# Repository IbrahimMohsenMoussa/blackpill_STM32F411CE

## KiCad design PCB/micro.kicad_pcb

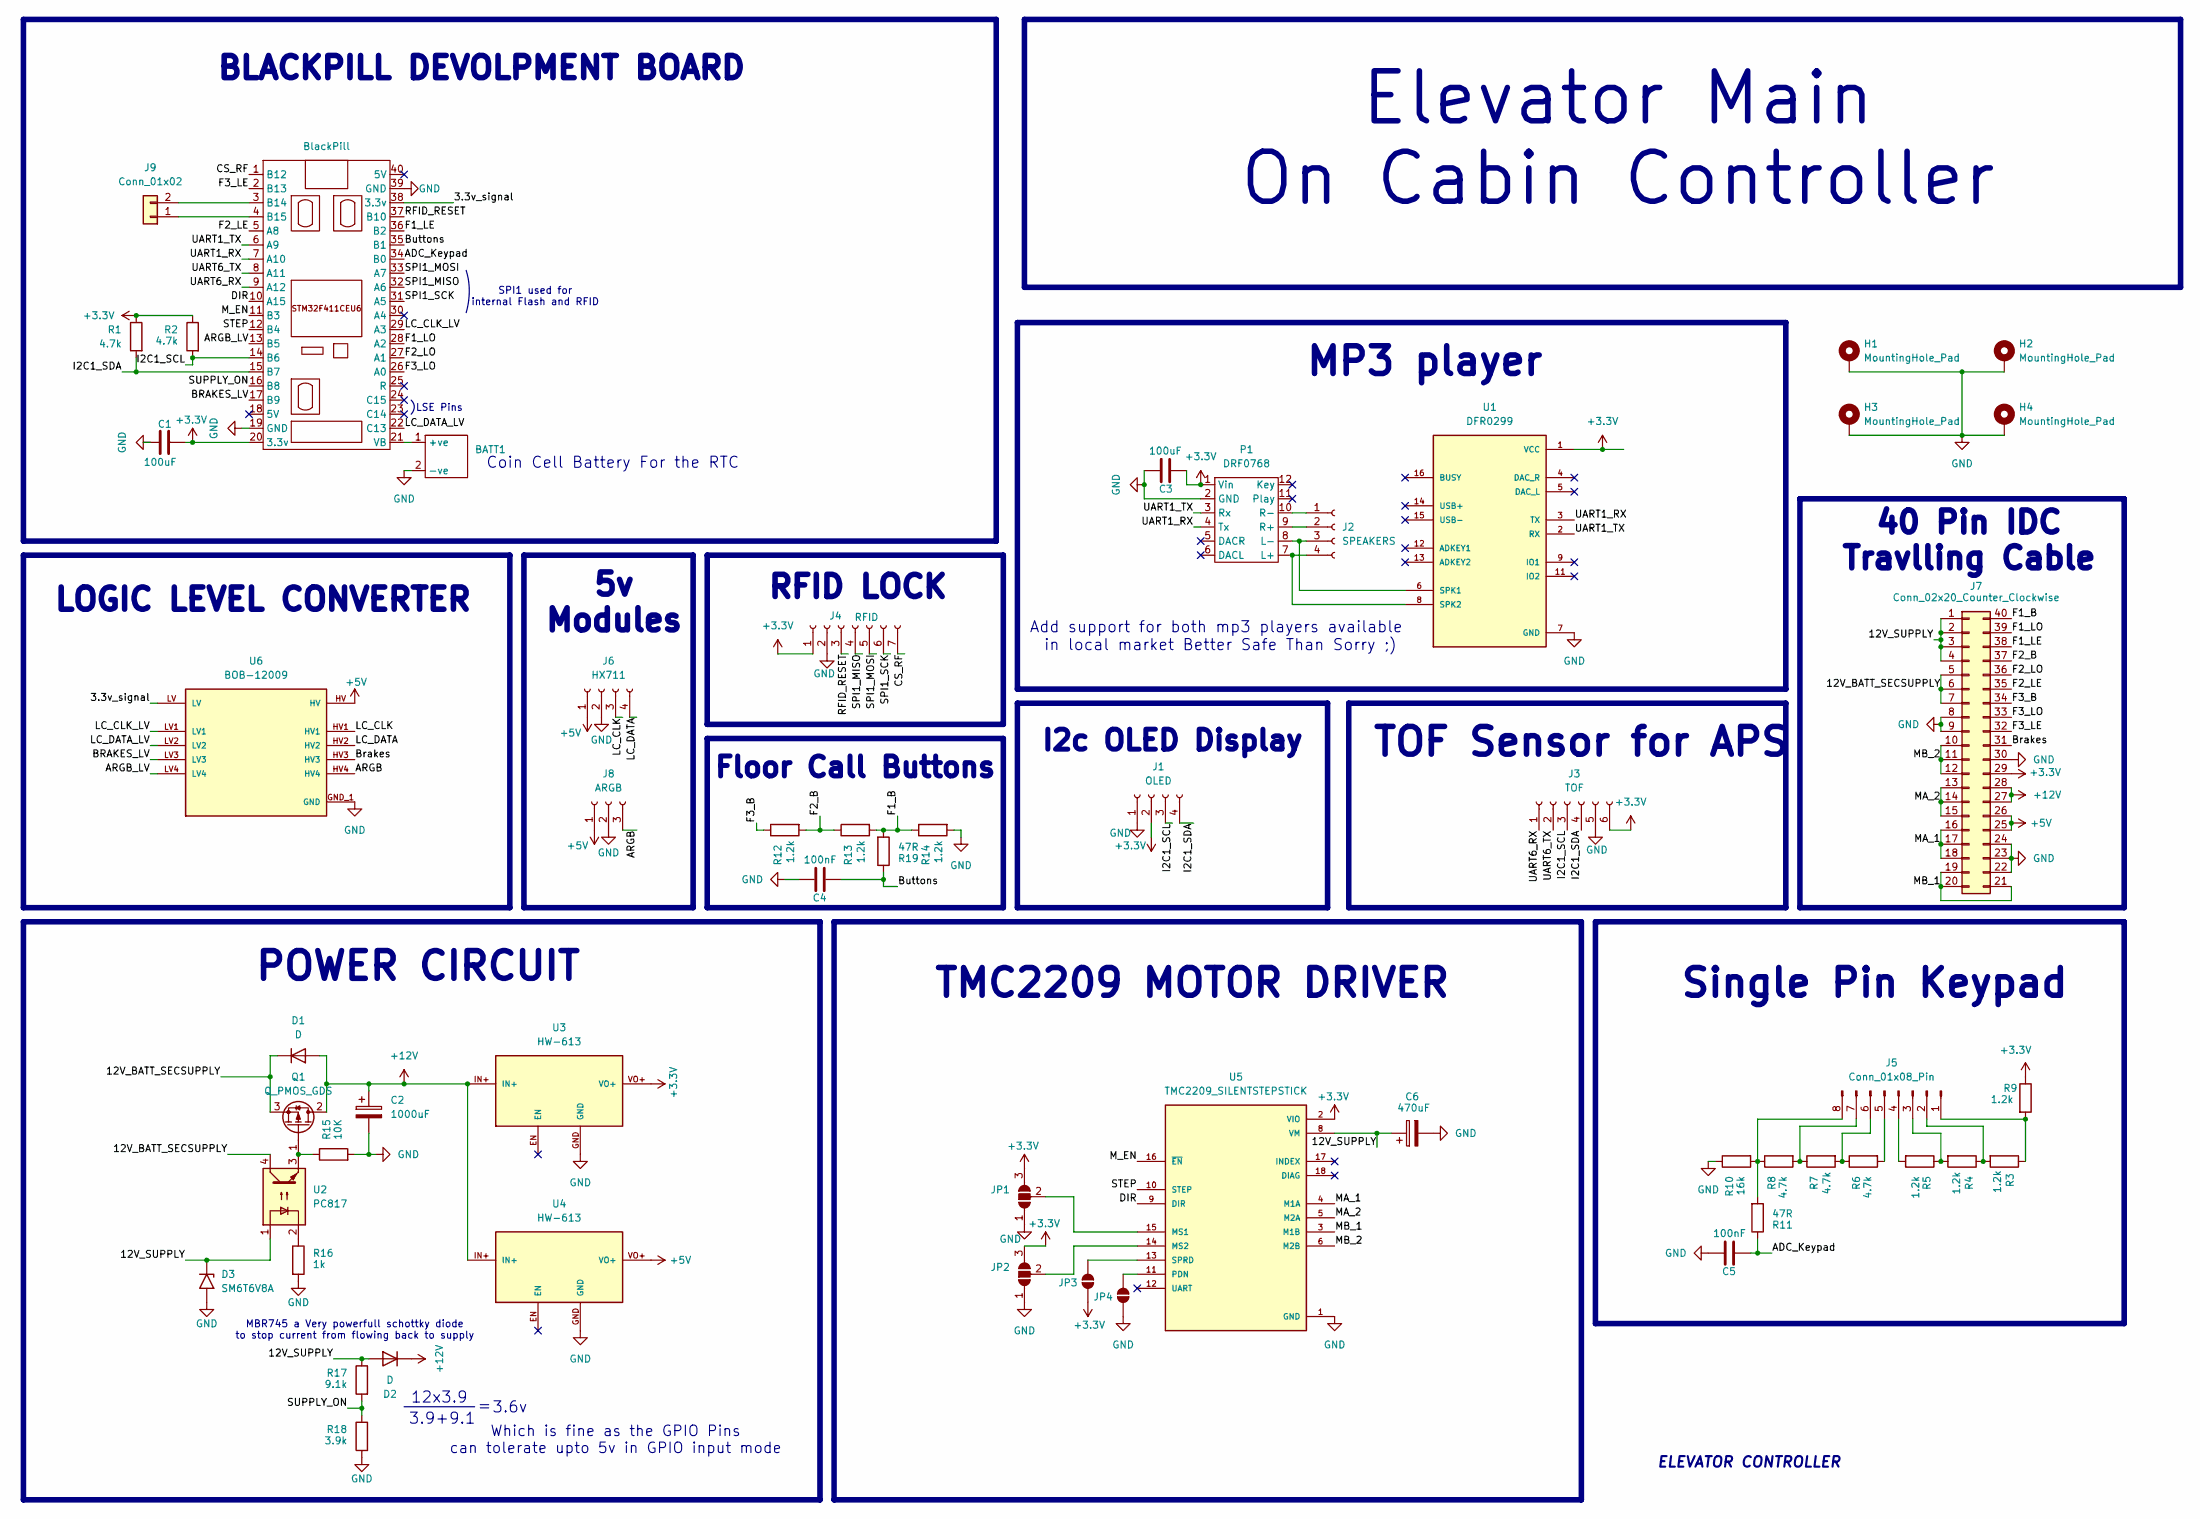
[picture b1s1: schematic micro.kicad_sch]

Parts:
BATT1: BatteryHolder_Keystone_103_1x20mm
C1, C3: 100uF; C_1206_3216Metric_Pad1.33x1.80mm_HandSolder
C2: 1000uF; CP_Radial_D12.5mm_P5.00mm
C4, C5: 100nF; C_1206_3216Metric_Pad1.33x1.80mm_HandSolder
C6: 470uF; CP_Radial_D8.0mm_P5.00mm
D1: D; D_DO-41_SOD81_P12.70mm_Horizontal
D2: D; TO-220F-2_Horizontal_TabDown
D3: SM6T6V8A; D_SMB
H1, H2, H3, H4: MountingHole_Pad; MountingHole_3.2mm_M3_ISO14580_Pad_TopBottom
J1: OLED; JST_XH_B4B-XH-AM_1x04_P2.50mm_Vertical
J2: SPEAKERS; JST_XH_B4B-XH-AM_1x04_P2.50mm_Vertical
J3: TOF; JST_XA_B06B-XASK-1-A_1x06_P2.50mm_Vertical
J4: RFID; JST_XA_B07B-XASK-1_1x07_P2.50mm_Vertical
J5: Conn_01x08_Pin; PinHeader_1x08_P2.54mm_Vertical
J6: HX711; JST_XH_B4B-XH-AM_1x04_P2.50mm_Vertical
J7: Conn_02x20_Counter_Clockwise; IDC-Header_2x20_P2.54mm_Horizontal
J8: ARGB; JST_XA_B03B-XASK-1_1x03_P2.50mm_Vertical
J9: Conn_01x02; JST_XA_B02B-XASK-1_1x02_P2.50mm_Vertical
JP1, JP2: SolderJumper_3_Open; SolderJumper-3_P1.3mm_Open_RoundedPad1.0x1.5mm_NumberLabels
JP3, JP4: SolderJumper_2_Open; SolderJumper-2_P1.3mm_Open_RoundedPad1.0x1.5mm
P1: DRF0768; DIP-12_913_ELL
Q1: Q_PMOS_GDS; TO-220-3_Horizontal_TabDown
R1, R2, R6, R7, R8: 4.7k; R_1206_3216Metric_Pad1.30x1.75mm_HandSolder
R3, R4, R5, R9, R12, R13, R14: 1.2k; R_1206_3216Metric_Pad1.30x1.75mm_HandSolder
R10: 16k; R_1206_3216Metric_Pad1.30x1.75mm_HandSolder
R11, R19: 47R; R_1206_3216Metric_Pad1.30x1.75mm_HandSolder
R15: 10K; R_1206_3216Metric_Pad1.30x1.75mm_HandSolder
R16: 1k; R_1206_3216Metric_Pad1.30x1.75mm_HandSolder
R17: 9.1k; R_1206_3216Metric_Pad1.30x1.75mm_HandSolder
R18: 3.9k; R_1206_3216Metric_Pad1.30x1.75mm_HandSolder
U1: DFR0299; MODULE_DFR0299
U2: PC817; DIP-4_W7.62mm
U3, U4: HW-613
U5: TMC2209_SILENTSTEPSTICK; MODULE_TMC2209_SILENTSTEPSTICK; PARTREV 1.20
U6: BOB-12009; CONV_BOB-12009; PARTREV 01
μC1: BlackPill; DIP-40_W15.24mm_LongPads

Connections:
+3.3V: C1.1, C3.1, J1.2, J3.6, J4.1, J7.29, JP1.3 (B), JP2.3 (B), JP3.1 (A), P1.1 (Vin), R1.1, R2.1, R9.1, U1.1 (VCC), U3.VO+, U5.2 (VIO), μC1.20 (3.3v)
+5V: J6.1, J7.25, J7.26, J8.1, U4.VO+, U6.HV
+12V: C2.1, D1.2 (A), D2.1 (K), J7.27, J7.28, Q1.2 (D), U3.IN+, U4.IN+
/3.3v_signal: U6.LV, μC1.38 (3.3v)
/12V_BATT_SECSUPPLY: D1.1 (K), J7.5, J7.6, J7.7, Q1.3 (S), U2.4
/12V_SUPPLY: C6.1, D2.2 (A), D3.1 (A1), J7.1, J7.2, J7.3, J7.4, R17.1, U2.1, U5.8 (VM)
/ADC_Keypad: C5.2, R11.1, μC1.34 (B0)
/ARGB: J8.3, U6.HV4
/ARGB_LV: U6.LV4, μC1.13 (B5)
/BRAKES_LV: U6.LV3, μC1.17 (B9)
/Brakes: J7.31, U6.HV3
/Buttons: C4.2, R19.1, μC1.35 (B1)
/CS_RF: J4.7, μC1.1 (B12)
/DIR: U5.9 (DIR), μC1.10 (A15)
/F1_B: J7.40, R13.2, R14.1, R19.2
/F1_LE: J7.38, μC1.36 (B2)
/F1_LO: J7.39, μC1.28 (A2)
/F2_B: J7.37, R12.2, R13.1
/F2_LE: J7.35, μC1.5 (A8)
/F2_LO: J7.36, μC1.27 (A1)
/F3_B: J7.34, R12.1
/F3_LE: J7.32, μC1.2 (B13)
/F3_LO: J7.33, μC1.26 (A0)
/I2C1_SCL: J1.3, J3.3, R2.2, μC1.14 (B6)
/I2C1_SDA: J1.4, J3.4, R1.2, μC1.15 (B7)
/LC_CLK: J6.3, U6.HV1
/LC_CLK_LV: U6.LV1, μC1.29 (A3)
/LC_DATA: J6.4, U6.HV2
/LC_DATA_LV: U6.LV2, μC1.22 (C13)
/MA_1: J7.16, J7.17, J7.18, U5.4 (M1A)
/MA_2: J7.13, J7.14, J7.15, U5.5 (M2A)
/MB_1: J7.19, J7.20, J7.21, U5.3 (M1B)
/MB_2: J7.10, J7.11, J7.12, U5.6 (M2B)
/M_EN: U5.16 (~EN), μC1.11 (B3)
/RFID_RESET: J4.3, μC1.37 (B10)
/SPI1_MISO: J4.4, μC1.32 (A6)
/SPI1_MOSI: J4.5, μC1.33 (A7)
/SPI1_SCK: J4.6, μC1.31 (A5)
/STEP: U5.10 (STEP), μC1.12 (B4)
/SUPPLY_ON: R17.2, R18.1, μC1.16 (B8)
/UART1_RX: P1.4 (Tx), U1.3 (TX), μC1.7 (A10)
/UART1_TX: P1.3 (Rx), U1.2 (RX), μC1.6 (A9)
/UART6_RX: J3.1, μC1.9 (A12)
/UART6_TX: J3.2, μC1.8 (A11)
GND: BATT1.2 (-ve), C1.2, C2.2, C3.2, C4.1, C5.1, C6.2, D3.2 (A2), H1.1, H2.1, H3.1, H4.1, J1.1, J3.5, J4.2, J6.2, J7.8, J7.9, J7.22, J7.23, J7.24, J7.30, J8.2, JP1.1 (A), JP2.1 (A), JP4.1 (A), P1.2 (GND), R10.1, R14.2, R15.2, R16.2, R18.2, U1.7 (GND), U1.10 (GND), U3.GND, U4.GND, U5.1 (GND), U5.7 (GND), U6.GND_1 (GND), U6.GND_2 (GND), μC1.19 (GND), μC1.39 (GND)
unnamed: BATT1.1 (+ve), μC1.21 (VB)
unnamed: J2.1, P1.10 (R-)
unnamed: J2.2, P1.9 (R+)
unnamed: J2.3, P1.8 (L-), U1.6 (SPK1)
unnamed: J2.4, P1.7 (L+), U1.8 (SPK2)
unnamed: J5.1, R3.1, R9.2
unnamed: J5.2, R3.2, R4.1
unnamed: J5.3, R4.2, R5.1
unnamed: J5.4, R5.2
unnamed: J5.5, R6.2
unnamed: J5.6, R6.1, R7.2
unnamed: J5.7, R7.1, R8.2
unnamed: J5.8, R8.1, R10.2, R11.2
unnamed: J9.1, μC1.4 (B15)
unnamed: J9.2, μC1.3 (B14)
unnamed: JP1.2 (C), U5.15 (MS1)
unnamed: JP2.2 (C), U5.14 (MS2)
unnamed: JP3.2 (B), U5.13 (SPRD)
unnamed: JP4.2 (B), U5.11 (PDN)
unnamed: Q1.1 (G), R15.1, U2.3
unnamed: R16.1, U2.2

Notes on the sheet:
Floor Call Buttons
LOGIC LEVEL CONVERTER
Which is fine as the GPIO Pins can tolerate upto 5v in GPIO input mode
ELEVATOR CONTROLLER
5v Modules
Coin Cell Battery For the RTC
3.6v
POWER CIRCUIT
MBR745 a Very powerfull schottky diode to stop current from flowing back to supply
SPI1 used for internal Flash and RFID
TOF Sensor for APS
LSE Pins
TMC2209 MOTOR DRIVER
I2c OLED Display
12x3.9
Single Pin Keypad
Add support for both mp3 players available in local market Better Safe Than Sorry ;)
RFID LOCK
Elevator Main On Cabin Controller
MP3 player
3.9+9.1
BLACKPILL DEVOLPMENT BOARD
40 Pin IDC Travlling Cable

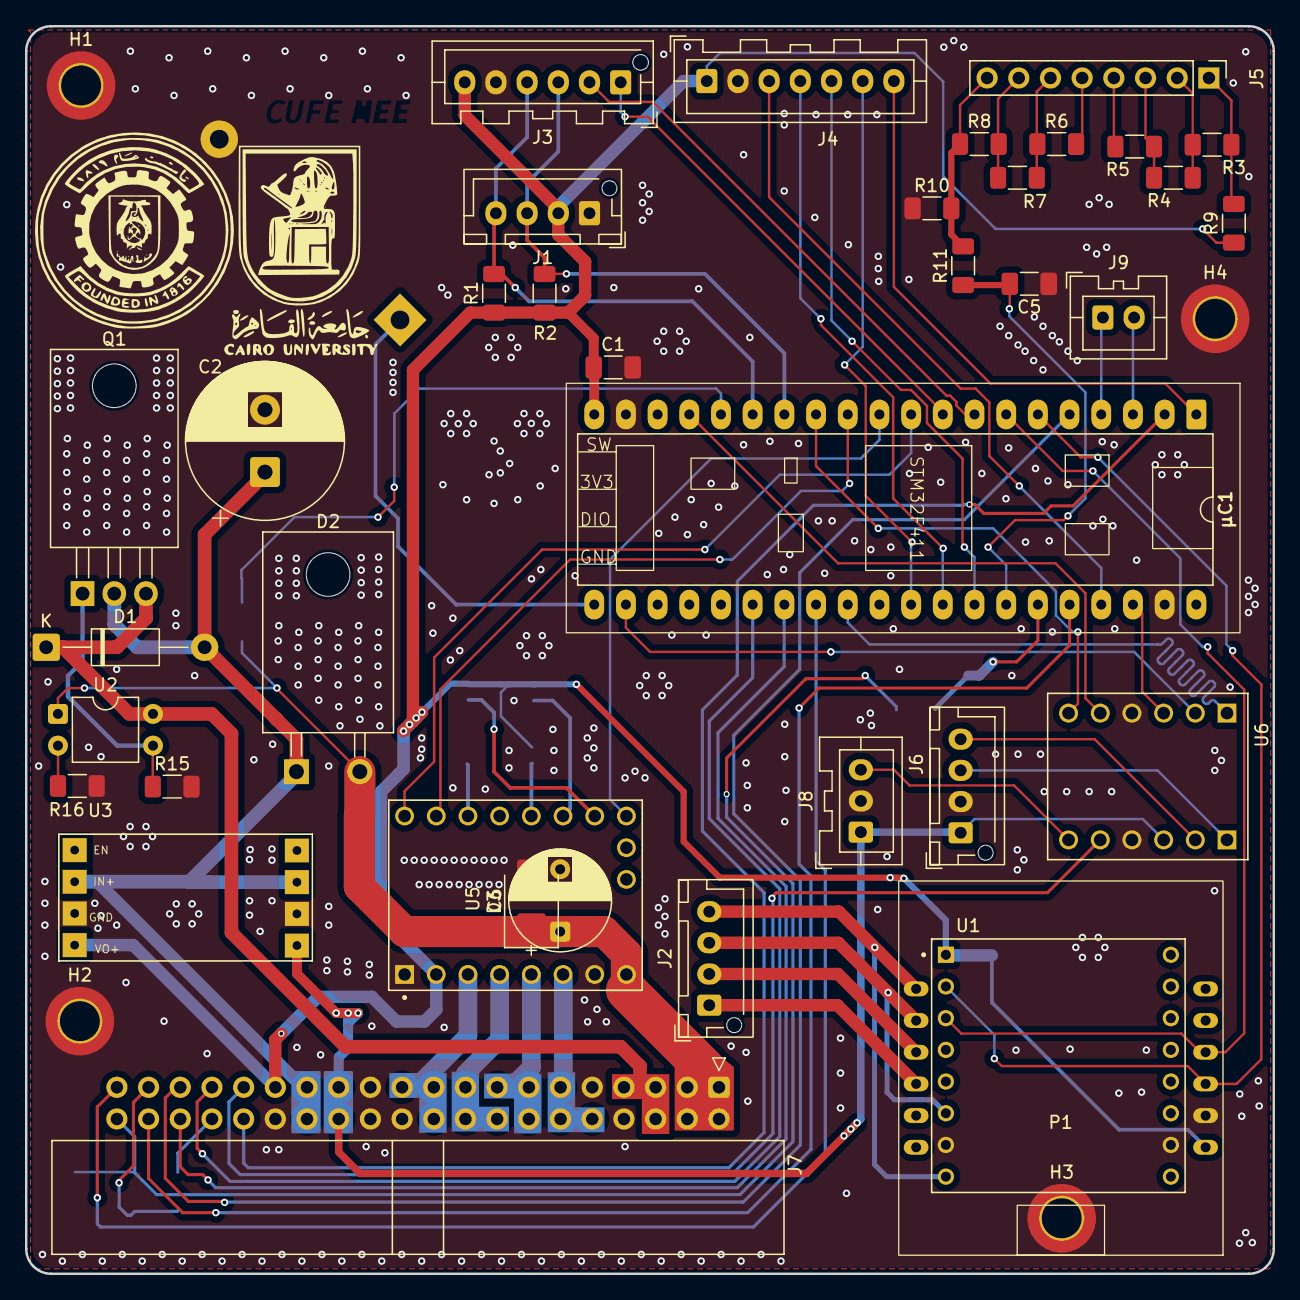
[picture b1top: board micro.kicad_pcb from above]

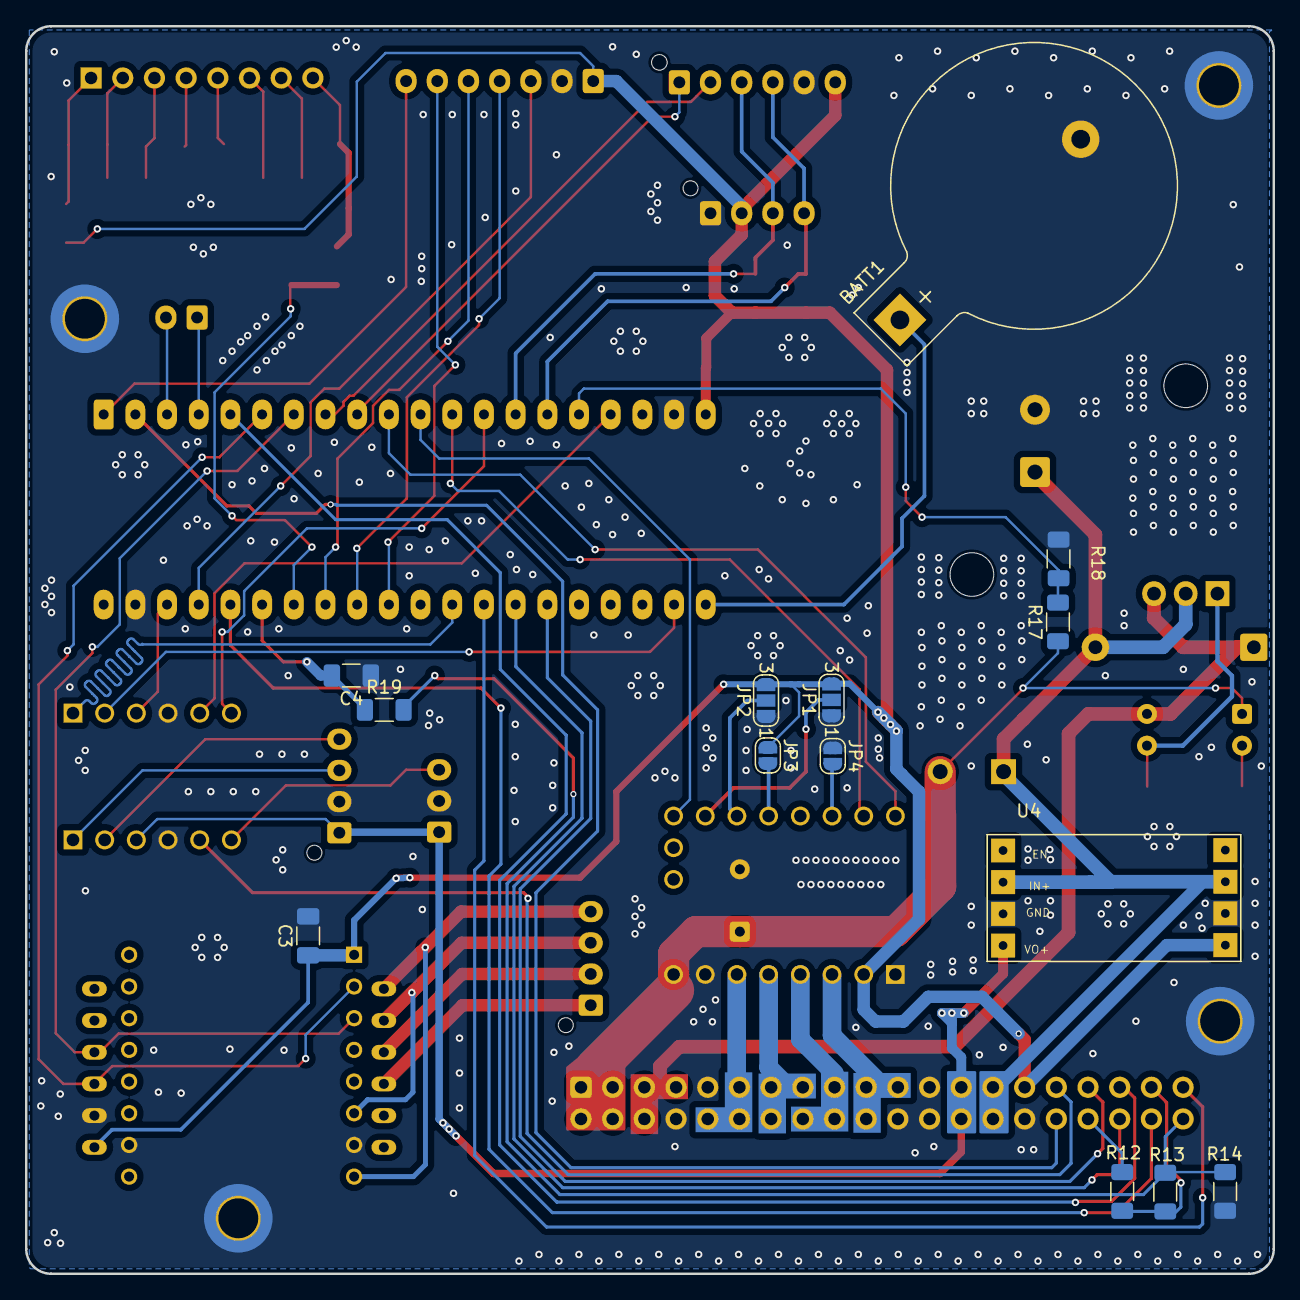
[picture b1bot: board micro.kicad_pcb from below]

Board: 2 copper layers, 100.0 x 100.0 mm, 55 parts (14 on the bottom side), 66 nets.

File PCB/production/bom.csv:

Designator,Footprint,Quantity,Value,LCSC Part #
BATT1,BatteryHolder_Keystone_103_1x20mm,1,~,
"C1, C3",1206,2,100uF,
C2,CP_Radial_D12.5mm_P5.00mm,1,1000uF,
"C4, C5",1206,2,100nF,
C6,CP_Radial_D8.0mm_P5.00mm,1,470uF,
D1,D_DO-41_SOD81_P12.70mm_Horizontal,1,D,
D2,TO-220F-2_Horizontal_TabDown,1,D,
J1,JST_XH_B4B-XH-AM_1x04_P2.50mm_Vertical,1,OLED,
J2,JST_XH_B4B-XH-AM_1x04_P2.50mm_Vertical,1,SPEAKERS,
J3,JST_XA_B06B-XASK-1-A_1x06_P2.50mm_Vertical,1,TOF,
J4,JST_XA_B07B-XASK-1_1x07_P2.50mm_Vertical,1,RFID,
J5,PinHeader_1x08_P2.54mm_Vertical,1,Conn_01x08_Pin,
J6,JST_XH_B4B-XH-AM_1x04_P2.50mm_Vertical,1,HX711,
J7,IDC-Header_2x20_P2.54mm_Horizontal,1,Conn_02x20_Counter_Clockwise,
J8,JST_XA_B03B-XASK-1_1x03_P2.50mm_Vertical,1,ARGB,
J9,JST_XA_B02B-XASK-1_1x02_P2.50mm_Vertical,1,Conn_01x02,
P1,DIP-12_913_ELL,1,DRF0768,
Q1,TO-220-3_Horizontal_TabDown,1,Q_PMOS_GDS,
"R1, R2, R6, R7, R8",1206,5,4.7k,
R10,1206,1,16k,
"R11, R19",1206,2,47R,
"R12, R13, R14, R3, R4, R5, R9",1206,7,1.2k,
R15,1206,1,10K,
R16,1206,1,1k,
R17,1206,1,9.1k,
R18,1206,1,3.9k,
U1,MODULE_DFR0299,1,DFR0299,
U2,DIP-4_W7.62mm,1,PC817,
"U3, U4",HW-613,2,HW-613,
U5,MODULE_TMC2209_SILENTSTEPSTICK,1,TMC2209_SILENTSTEPSTICK,
U6,CONV_BOB-12009,1,BOB-12009,
ΜC1,DIP-40_W15.24mm_LongPads,1,BlackPill,

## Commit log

2026-03-01 intial_commit
2026-03-18 Systick waiting for test (needs some cleaning though)
2026-03-18 test push
2026-04-13 add to git ignore
2026-04-13 ignore
2026-04-13 Refactor RCC and System Clock Configuration
    - Commented out APB1 and APB2 prescaler definitions in rcc.asm for clarity.
    - Updated the prescaler configuration logic in rcc.asm to use bitwise OR instead of a custom operator.
    - Added CPU clock reference and prescaler value definitions in stm32f411.inc for better configurability.
    - Introduced derived frequency calculations for AHB and APB buses in stm32f411.inc.
    - Added SysTick assembly file for timer functionality.
    - Updated ninja build logs and configuration outputs to reflect recent changes.
2026-04-25 Add TOF400F driver and related assembly files for STM32F411
    - Implemented `tof.asm` for TOF400F laser ranging module, including USART6 initialization and Modbus communication.
    - Created `tof400f_driver.s` to handle distance reading from the TOF400F sensor.
    - Added assembly files for ADC, keypad, stepper, and timer functionalities.
    - Introduced object files for each module to facilitate compilation and linking.
    - Ensured proper USART configuration and data handling for reliable sensor communication.
2026-04-25 Enhance Timer and TOF400F Driver Functionality
    - Updated TIM3_PWM_Init to enable Auto-Reload Preload (ARPE) along with the timer.
    - Improved TOF_Read_Distance procedure:
    - Enhanced RX buffer flushing mechanism to ensure complete clearance of stale data.
    - Added timeout checks during transmission and reception to handle potential hangs.
    - Implemented validation checks for the response format to ensure data integrity before processing.
    - Introduced specific error code return on timeout scenarios.
2026-04-25 Add LED control and button reading functionality
    - Updated dio.asm to include definitions for three new LEDs (LED_F0, LED_F1, LED_F2).
    - Modified hardware_config.inc to define IDs for the new LEDs.
    - Implemented Read_Button_Values function in keypad.asm to read button states via ADC.
    - Enhanced main.asm to control LED states based on floor selection and button presses.
    - Updated port.asm to configure GPIO settings for the new LEDs.
2026-05-07 df player added,,,, the current main is for testing
2026-05-07 Add EXTI and Brakes modules for STM32F411
    - Implemented `exti.asm` for dynamic initialization of external interrupts (EXTI).
    - Added `brakes.asm` with stub functions for engaging and disengaging elevator brakes.
    - Updated CMake configuration to include new assembly files in the build process.
    - Modified `build.ninja` and `compile_commands.json` to reflect changes in object files.
    - Enhanced object library `Group_src` to include new modules.
2026-05-07 Clean project: removed build artifacts and added startup changes
2026-05-07 Final build-ready version with organized directory structure
2026-05-07 Add build directory placeholder and update ignore rules
2026-05-07 implemented basic functionality for mpu6050 under mpu6050.asm, also added required read functions in i2c.asm, waiting for test (this tests the sensor working not actual logic)
2026-05-07 added 2 yml files for ibrahim, hindly back your 4 yml files before merging
2026-05-07 try this (no context can explain)
2026-05-07 modified git ignore so everyone won't see the .yml files and other keil files as well
2026-05-07 Delete project.uvprojx
    deleted last keil file
2026-05-07 i just wanna sleeep
2026-05-08 Update project files and correct hardware configuration
    - Updated the last updated timestamp in project.htm for accuracy.
    - Corrected the order of LED definitions in hardware_config.inc to maintain consistency.
    - Modified threshold values in keypad.asm for improved functionality.
    - Enhanced main.asm with additional UI functions for better user interaction and display updates during emergency and operational states.
    - Updated ninja log and dependencies to reflect recent changes and ensure build integrity.
2026-05-08 Add ID_POWER_MONITOR mapping and implement EXTI9_5_IRQHandler for emergency handling
2026-05-10 Add drivers for MPU6050 and Servo Motor, along with supporting files
    - Implemented MPU6050 driver in assembly for STM32F411, including initialization and raw accelerometer reading functions.
    - Created Servo Motor driver for controlling elevator doors, with functions to open and close doors based on floor number.
    - Added necessary assembly files for data memory and FFT calculations.
    - Compiled object files for load cell and servo driver functionalities.
2026-05-10 Add SPI1 driver implementation for STM32F411
    - Implemented SPI1 driver in assembly language, providing functions for initialization, data transmission, and control of the MFRC522 RFID module.
    - Added functions: SPI1_Init, SPI1_TransmitReceive, SPI1_Transmit, SPI1_Receive, SPI1_CS_Assert, SPI1_CS_Deassert, SPI1_RST_Assert, and SPI1_RST_Deassert.
    - Configured SPI1 for master mode, Mode 0 operation, and software NSS management.
    - Included necessary dependencies and constants for SPI operation.
    - Compiled and generated object files for the SPI1 driver and MFRC522 module.
2026-05-10 Update project files and main assembly for keypad security features
    - Updated project.htm to reflect the latest build timestamp and corrected function references in the call graph.
    - Modified main.asm to introduce a keypad unlocking mechanism using RFID.
    - Added Sys_Keypad_Unlocked variable to track the keypad state.
    - Implemented RFID polling for authorized cards to unlock the keypad.
    - Removed the previous card polling loop and replaced it with security verification logic.
    - Added feedback sounds for authorized and unauthorized access attempts.
2026-05-13 Update project files and source code
    - Updated project.htm to reflect the new last updated timestamp.
    - Added new track definitions TRACK_DENIED and TRACK_GRANTED in DFPlayer_defs.s.
    - Adjusted control loop constant CL_KP from 28 to 25 in main.asm.
    - Modified soft start threshold from 95 to 80 in main.asm.
    - Changed success sound track to TRACK_GRANTED and error buzz track to TRACK_DENIED in main.asm.
    - Updated error handling for locked keypad in main.asm.
